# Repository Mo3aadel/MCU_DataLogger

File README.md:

# MCU_DataLogger
A PCB board that consists of ATMEGA328P-AU ,  RTC module and 2 external EEPROMS for saving time 
ART OF PCB DESIGN

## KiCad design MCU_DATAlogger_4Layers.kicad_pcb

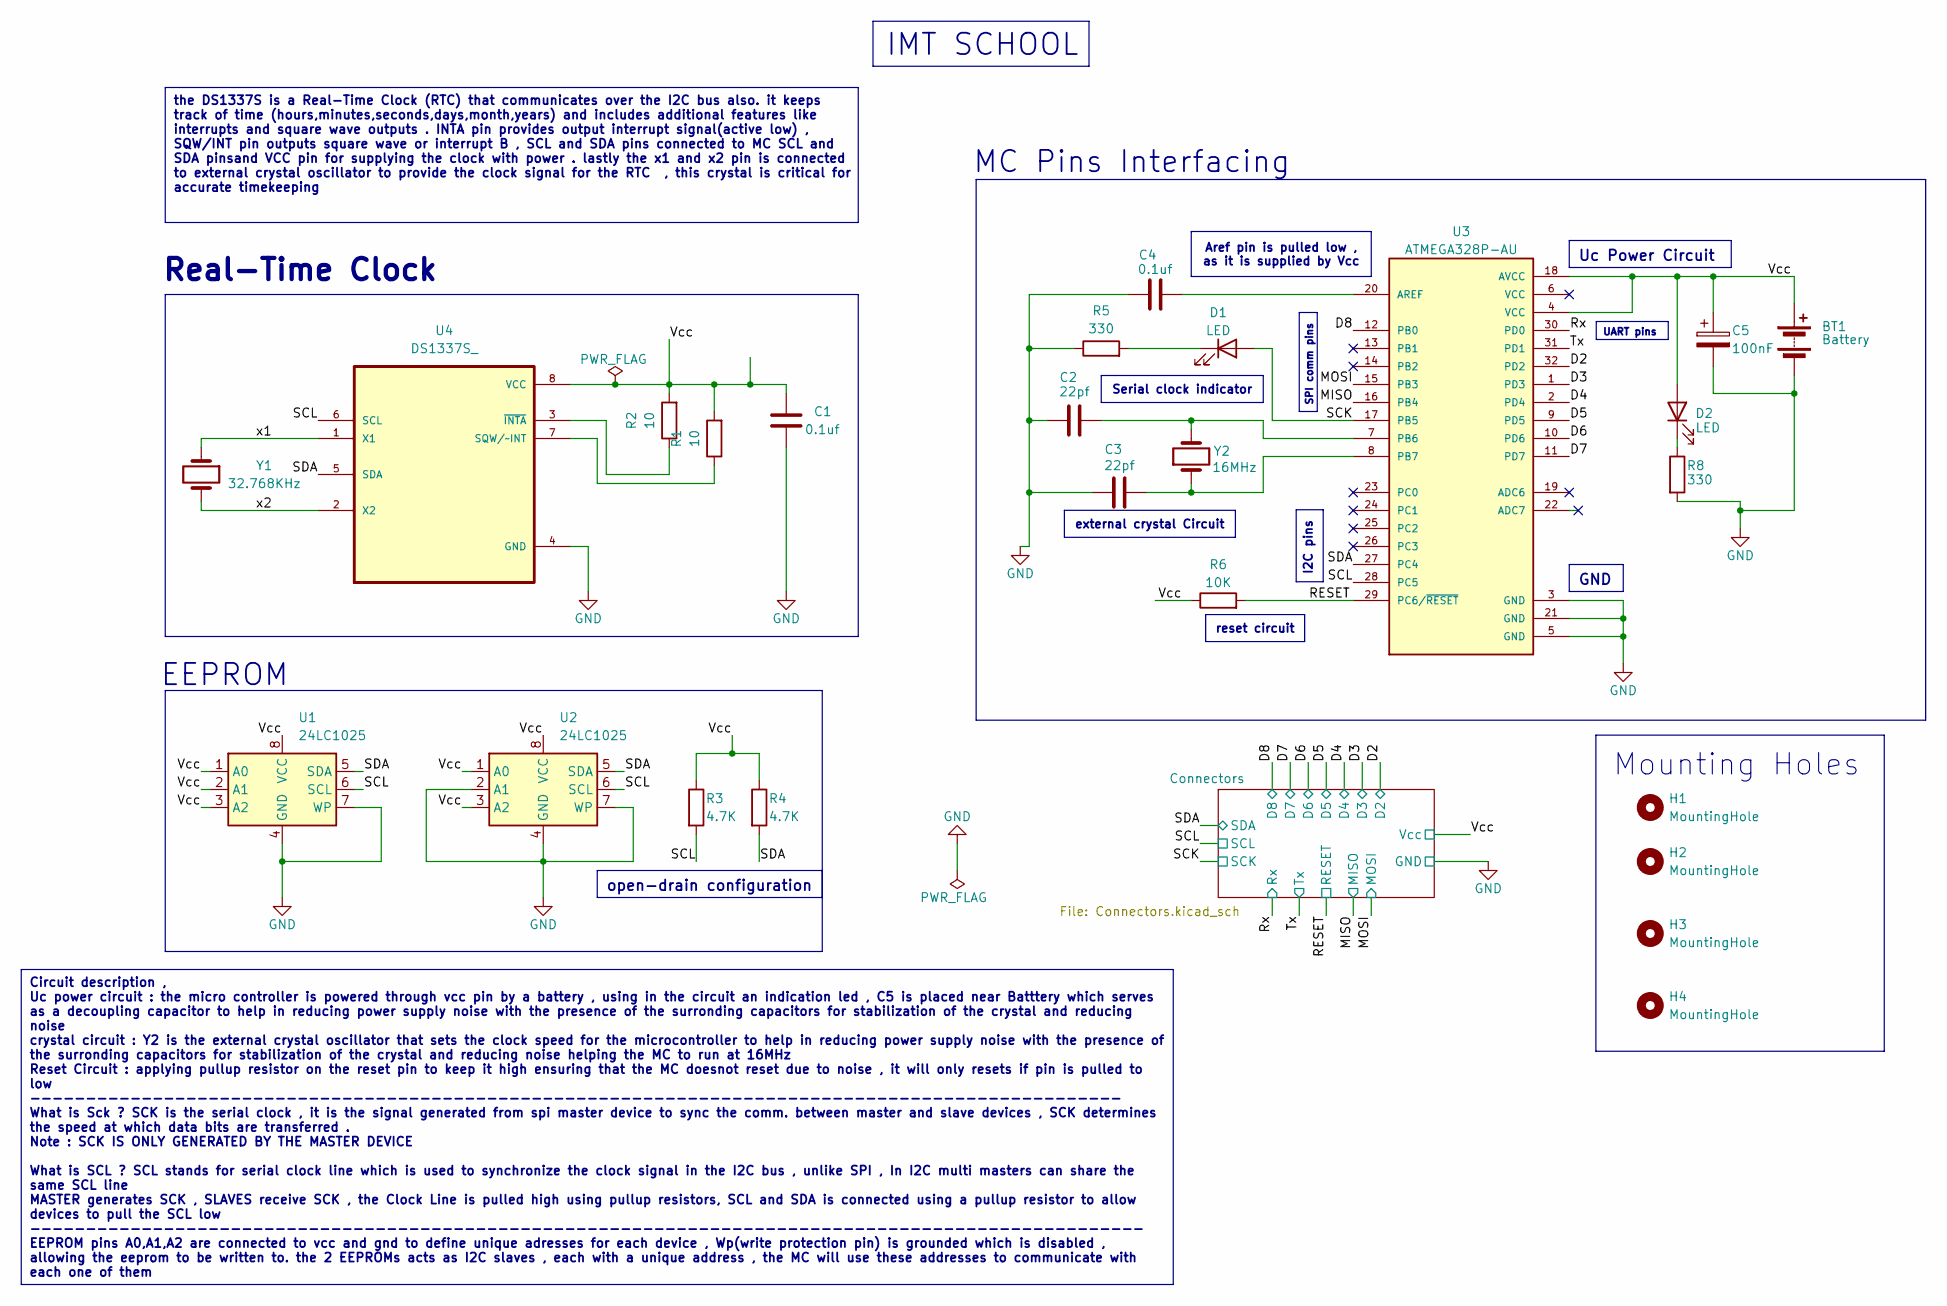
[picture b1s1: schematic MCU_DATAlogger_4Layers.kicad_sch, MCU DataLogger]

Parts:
BT1: Battery; PinHeader_1x02_P2.54mm_Vertical
C1, C4: 0.1uf; C_0805_2012Metric
C2, C3: 22pf; C_0805_2012Metric
C5: 100nF; C_0805_2012Metric
D1, D2: LED; LED_0805_2012Metric
H1, H2, H3, H4: MountingHole; MountingHole_2.1mm
R1, R2: 10; R_0805_2012Metric
R3, R4: 4.7K; R_0805_2012Metric
R5, R8: 330; R_0805_2012Metric
R6: 10K; R_0805_2012Metric
U1, U2: 24LC1025; SOIC-8_5.23x5.23mm_P1.27mm
U3: ATMEGA328P-AU; QFP80P900X900X120-32N; PARTREV 8271A
U4: DS1337S_; SOIC127P600X175-8N
Y1: 32.768KHz; Crystal_SMD_5032-2Pin_5.0x3.2mm_HandSoldering
Y2: 16MHz; Crystal_SMD_5032-2Pin_5.0x3.2mm_HandSoldering

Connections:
/D2: U3.32 (PD2); also elsewhere on the board
/D3: U3.1 (PD3); also elsewhere on the board
/D4: U3.2 (PD4); also elsewhere on the board
/D5: U3.9 (PD5); also elsewhere on the board
/D6: U3.10 (PD6); also elsewhere on the board
/D7: U3.11 (PD7); also elsewhere on the board
/D8: U3.12 (PB0); also elsewhere on the board
/MISO: U3.16 (PB4); also elsewhere on the board
/MOSI: U3.15 (PB3); also elsewhere on the board
/RESET: R6.2, U3.29 (PC6/~RESET); also elsewhere on the board
/Rx: U3.30 (PD0); also elsewhere on the board
/SCK: D1.2 (A), U3.17 (PB5); also elsewhere on the board
/SCL: R3.2, U1.6 (SCL), U2.6 (SCL), U3.28 (PC5), U4.6 (SCL); also elsewhere on the board
/SDA: R4.2, U1.5 (SDA), U2.5 (SDA), U3.27 (PC4), U4.5 (SDA); also elsewhere on the board
/Tx: U3.31 (PD1); also elsewhere on the board
/Vcc: BT1.1 (+), C1.1, C5.1, D2.2 (A), R1.2, R2.2, R3.1, R4.1, R6.1, U1.1 (A0), U1.2 (A1), U1.3 (A2), U1.8 (VCC), U2.1 (A0), U2.3 (A2), U2.8 (VCC), U3.4 (VCC), U3.18 (AVCC), U4.8 (VCC); also elsewhere on the board
/x1: U4.1 (X1), Y1.1
/x2: U4.2 (X2), Y1.2
GND: BT1.2 (-), C1.2, C2.1, C3.1, C4.1, C5.2, R5.1, R8.2, U1.4 (GND), U1.7 (WP), U2.2 (A1), U2.4 (GND), U2.7 (WP), U3.3 (GND), U3.5 (GND), U3.21 (GND), U4.4 (GND); also elsewhere on the board
unnamed: D1.1 (K), R5.2
unnamed: D2.1 (K), R8.1
unnamed: C4.2, U3.20 (AREF)
unnamed: C2.2, U3.7 (PB6), Y2.2
unnamed: C3.2, U3.8 (PB7), Y2.1
unnamed: R1.1, U4.7 (SQW/~INT)
unnamed: R2.1, U4.3 (~INTA)

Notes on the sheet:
Aref pin is pulled low , as it is supplied by Vcc
Serial clock indicator
the DS1337S is a Real-Time Clock (RTC) that communicates over the I2C bus also. it keeps track of time (hours,minutes,seconds,days,month,years) and includes additional features like interrupts and square wave outputs . INTA pin provides output interrupt signal(active low) , SQW/INT pin outputs squa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
external crystal Circuit
SPI comm pins
reset circuit
Uc Power Circuit
I2C pins
UART pins
Mounting Holes
Circuit description , Uc power circuit : the micro controller is powered through vcc pin by a battery , using in the circuit an indication led , C5 is placed near Batttery which serves as a decoupling capacitor to help in reducing power supply noise with the presence of the surronding capacitors fo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
GND
open-drain configuration
MC Pins Interfacing
IMT SCHOOL
EEPROM
Real-Time Clock

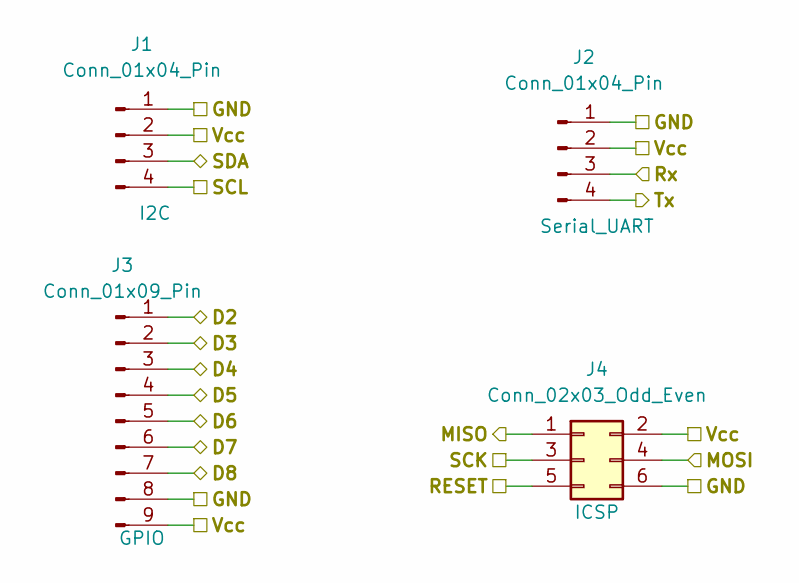
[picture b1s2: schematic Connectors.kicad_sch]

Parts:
J1, J2: Conn_01x04_Pin; PinHeader_1x04_P2.54mm_Vertical
J3: Conn_01x09_Pin; PinHeader_1x09_P2.54mm_Vertical
J4: Conn_02x03_Odd_Even; PinHeader_2x03_P2.54mm_Vertical

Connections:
/D2: J3.1; also elsewhere on the board
/D3: J3.2; also elsewhere on the board
/D4: J3.3; also elsewhere on the board
/D5: J3.4; also elsewhere on the board
/D6: J3.5; also elsewhere on the board
/D7: J3.6; also elsewhere on the board
/D8: J3.7; also elsewhere on the board
/MISO: J4.1; also elsewhere on the board
/MOSI: J4.4; also elsewhere on the board
/RESET: J4.5; also elsewhere on the board
/Rx: J2.3; also elsewhere on the board
/SCK: J4.3; also elsewhere on the board
/SCL: J1.4; also elsewhere on the board
/SDA: J1.3; also elsewhere on the board
/Tx: J2.4; also elsewhere on the board
/Vcc: J1.2, J2.2, J3.9, J4.2; also elsewhere on the board
GND: J1.1, J2.1, J3.8, J4.6; also elsewhere on the board

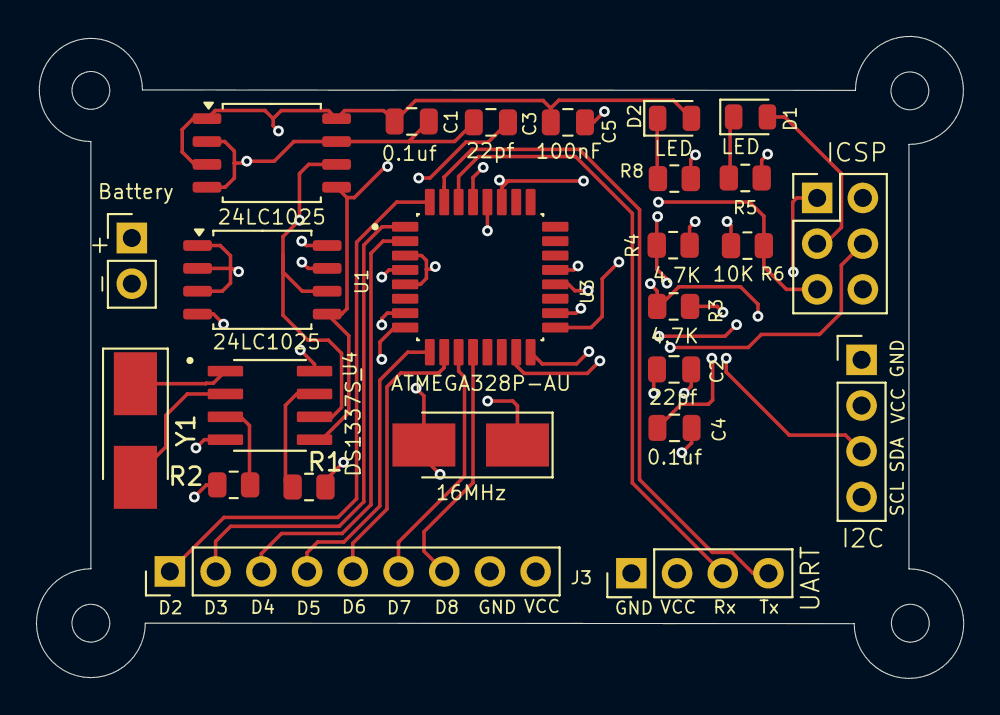
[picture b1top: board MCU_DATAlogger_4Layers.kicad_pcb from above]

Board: 4 copper layers, 51.5 x 35.7 mm, 29 parts (0 on the bottom side), 26 nets.

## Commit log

2024-12-23 Added a text box and some information on the page
2024-12-23 Added new IMT Logo on the layout design
2024-12-23 deleted some info.
2024-12-23 Added text on Readme file
2024-12-27 added some backup files
